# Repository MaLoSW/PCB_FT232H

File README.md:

# PCB_FT232H
KiCAD source files for a PCB board to work with FT232H chip ;)

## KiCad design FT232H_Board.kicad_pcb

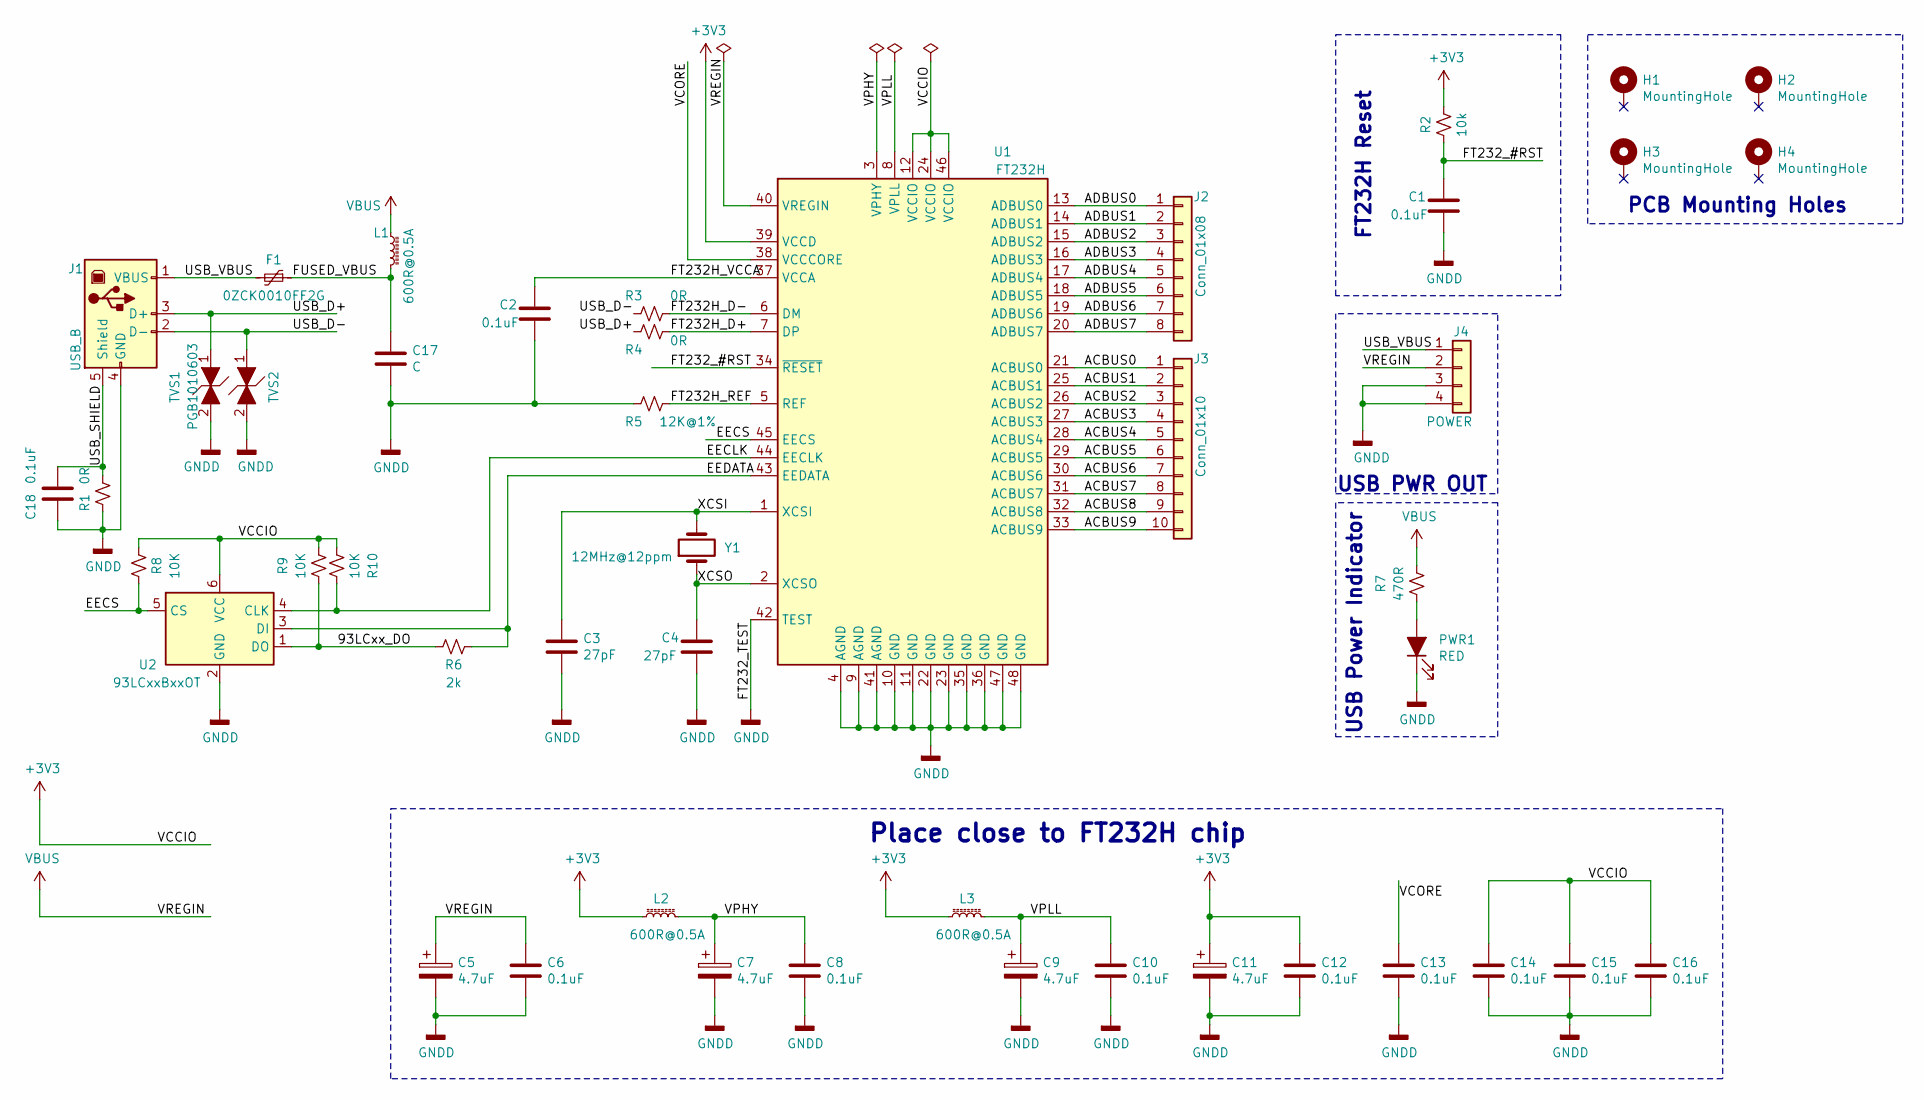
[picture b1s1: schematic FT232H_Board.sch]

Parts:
C1, C2, C6, C8, C10, C12, C13, C14, C15, C16, C18: 0.1uF; C_0603_1608Metric_Pad1.05x0.95mm_HandSolder
C3, C4: 27pF; C_0603_1608Metric_Pad1.05x0.95mm_HandSolder
C5, C9: 4.7uF; CP_EIA-1608-08_AVX-J_Pad1.25x1.05mm_HandSolder
C7, C11: 4.7uF; CP_EIA-1608-10_AVX-L_Pad1.25x1.05mm_HandSolder
C17: C; C_0603_1608Metric_Pad1.05x0.95mm_HandSolder
F1: 0ZCK0010FF2G; Fuse_0805_2012Metric_Pad1.15x1.40mm_HandSolder
H1, H2, H3, H4: MountingHole; MountingHole_3.2mm_M3_Pad_Via
J1: USB_B; USB_B_KYCON_KUSBX-SMT-BS1N
J2: Conn_01x08; PinHeader_1x08_P2.54mm_Vertical
J3: Conn_01x10; PinHeader_1x10_P2.54mm_Vertical
J4: POWER; PinHeader_2x02_P2.54mm_Vertical
L1, L2, L3: 600R@0.5A; L_0603_1608Metric_Pad1.05x0.95mm_HandSolder
PWR1: RED; LED_0805_2012Metric_Pad1.15x1.40mm_HandSolder
R1, R3, R4: 0R; R_0805_2012Metric_Pad1.20x1.40mm_HandSolder
R2: 10k; R_0805_2012Metric_Pad1.20x1.40mm_HandSolder
R5: 12K@1%; R_0805_2012Metric_Pad1.20x1.40mm_HandSolder
R6: 2k; R_0805_2012Metric_Pad1.20x1.40mm_HandSolder
R7: 470R; R_0805_2012Metric_Pad1.20x1.40mm_HandSolder
R8, R9, R10: 10K; R_0805_2012Metric_Pad1.20x1.40mm_HandSolder
TVS1, TVS2: PGB1010603; D_0603_1608Metric_Pad1.05x0.95mm_HandSolder
U1: FT232H; LQFP-48_7x7mm_P0.5mm
U2: 93LCxxBxxOT; SOT-23-6_Handsoldering
Y1: 12MHz@12ppm; Crystal_SMD_5032-2Pin_5.0x3.2mm_HandSoldering

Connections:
+3V3: C11.1, C12.1, C14.1, C15.1, C16.1, L2.1, L3.1, R2.2, R8.2, R9.2, R10.2, U1.12 (VCCIO), U1.24 (VCCIO), U1.39 (VCCD), U1.46 (VCCIO), U2.6 (VCC)
/93LCxx_DO: R6.1, R9.1, U2.1 (DO)
/ACBUS0: J3.1, U1.21 (ACBUS0)
/ACBUS1: J3.2, U1.25 (ACBUS1)
/ACBUS2: J3.3, U1.26 (ACBUS2)
/ACBUS3: J3.4, U1.27 (ACBUS3)
/ACBUS4: J3.5, U1.28 (ACBUS4)
/ACBUS5: J3.6, U1.29 (ACBUS5)
/ACBUS6: J3.7, U1.30 (ACBUS6)
/ACBUS7: J3.8, U1.31 (ACBUS7)
/ACBUS8: J3.9, U1.32 (ACBUS8)
/ACBUS9: J3.10, U1.33 (ACBUS9)
/ADBUS0: J2.1, U1.13 (ADBUS0)
/ADBUS1: J2.2, U1.14 (ADBUS1)
/ADBUS2: J2.3, U1.15 (ADBUS2)
/ADBUS3: J2.4, U1.16 (ADBUS3)
/ADBUS4: J2.5, U1.17 (ADBUS4)
/ADBUS5: J2.6, U1.18 (ADBUS5)
/ADBUS6: J2.7, U1.19 (ADBUS6)
/ADBUS7: J2.8, U1.20 (ADBUS7)
/EECLK: R10.1, U1.44 (EECLK), U2.4 (CLK)
/EECS: R8.1, U1.45 (EECS), U2.5 (CS)
/EEDATA: R6.2, U1.43 (EEDATA), U2.3 (DI)
/FT232H_D+: R4.1, U1.7 (DP)
/FT232H_D-: R3.1, U1.6 (DM)
/FT232H_REF: R5.2, U1.5 (REF)
/FT232H_VCCA: C2.1, U1.37 (VCCA)
/FT232_#RST: C1.1, R2.1, U1.34 (~RESET)
/FUSED_VBUS: C17.1, F1.1, L1.2
/USB_D+: J1.3 (D+), R4.2, TVS1.1
/USB_D-: J1.2 (D-), R3.2, TVS2.1
/USB_SHIELD: C18.1, J1.5 (Shield), R1.2
/USB_VBUS: F1.2, J1.1 (VBUS), J4.1
/VCORE: C13.1, U1.38 (VCCCORE)
/VPHY: C7.1, C8.1, L2.2, U1.3 (VPHY)
/VPLL: C9.1, C10.1, L3.2, U1.8 (VPLL)
/XCSI: C3.1, U1.1 (XCSI), Y1.2
/XCSO: C4.1, U1.2 (XCSO), Y1.1
GNDD: C1.2, C2.2, C3.2, C4.2, C5.2, C6.2, C7.2, C8.2, C9.2, C10.2, C11.2, C12.2, C13.2, C14.2, C15.2, C16.2, C17.2, C18.2, J1.4 (GND), J4.3, J4.4, PWR1.1 (K), R1.1, R5.1, TVS1.2, TVS2.2, U1.4 (AGND), U1.9 (AGND), U1.10 (GND), U1.11 (GND), U1.22 (GND), U1.23 (GND), U1.35 (GND), U1.36 (GND), U1.41 (AGND), U1.42 (TEST), U1.47 (GND), U1.48 (GND), U2.2 (GND)
unnamed: PWR1.2 (A), R7.1
VBUS: C5.1, C6.1, J4.2, L1.1, R7.2, U1.40 (VREGIN)

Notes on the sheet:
Place close to FT232H chip
USB Power Indicator
USB PWR OUT
FT232H Reset
PCB Mounting Holes

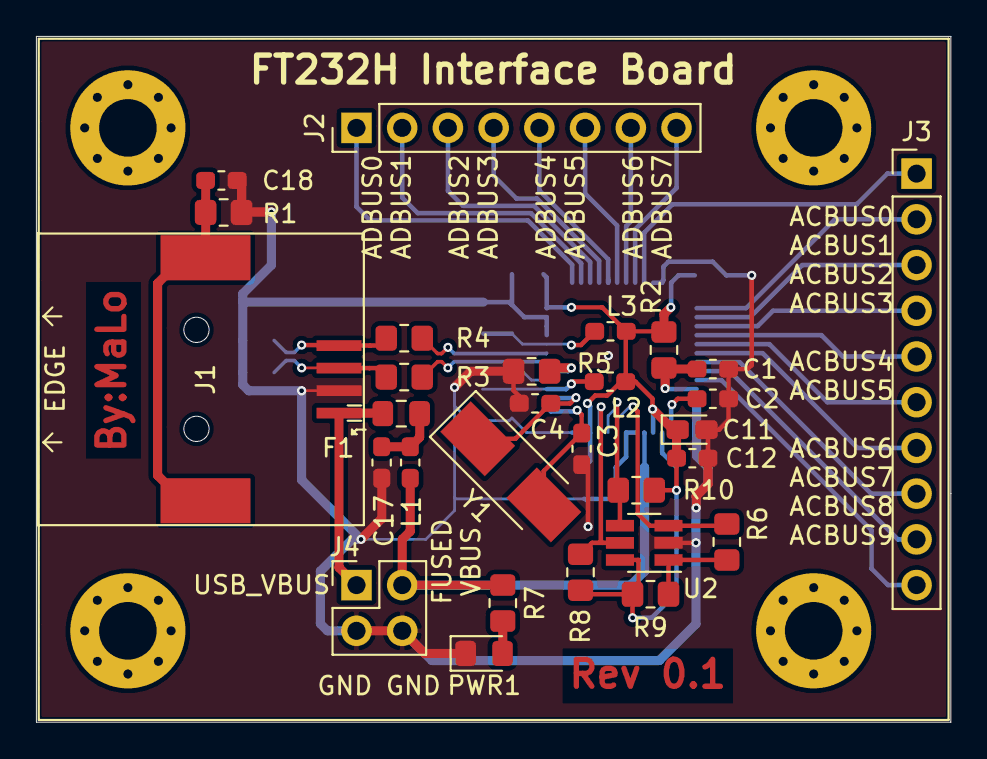
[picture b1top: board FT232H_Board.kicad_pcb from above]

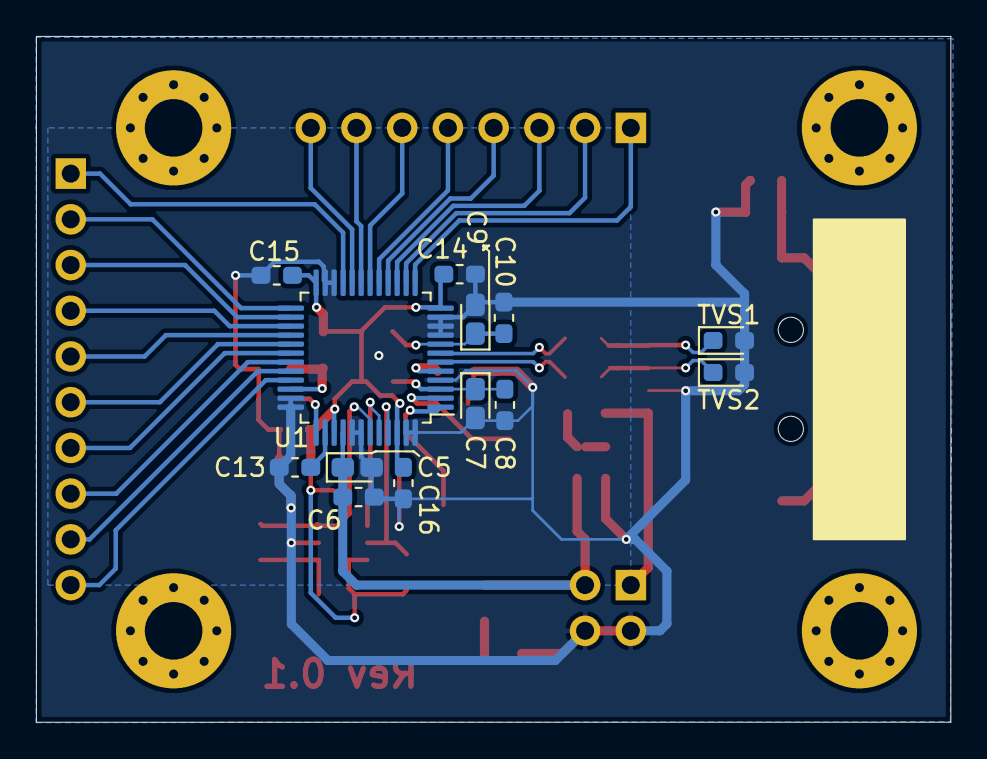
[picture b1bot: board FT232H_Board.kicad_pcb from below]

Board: 2 copper layers, 50.8 x 38.1 mm, 46 parts (13 on the bottom side), 41 nets.

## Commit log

2021-11-28 Committed original design ;)
